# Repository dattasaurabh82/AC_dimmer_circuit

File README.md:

# AC_dimmer_circuit

Deisgend quickly in 2016 for [Politics of Power](http://www.dattasaurabh.com/Politics-of-Power)

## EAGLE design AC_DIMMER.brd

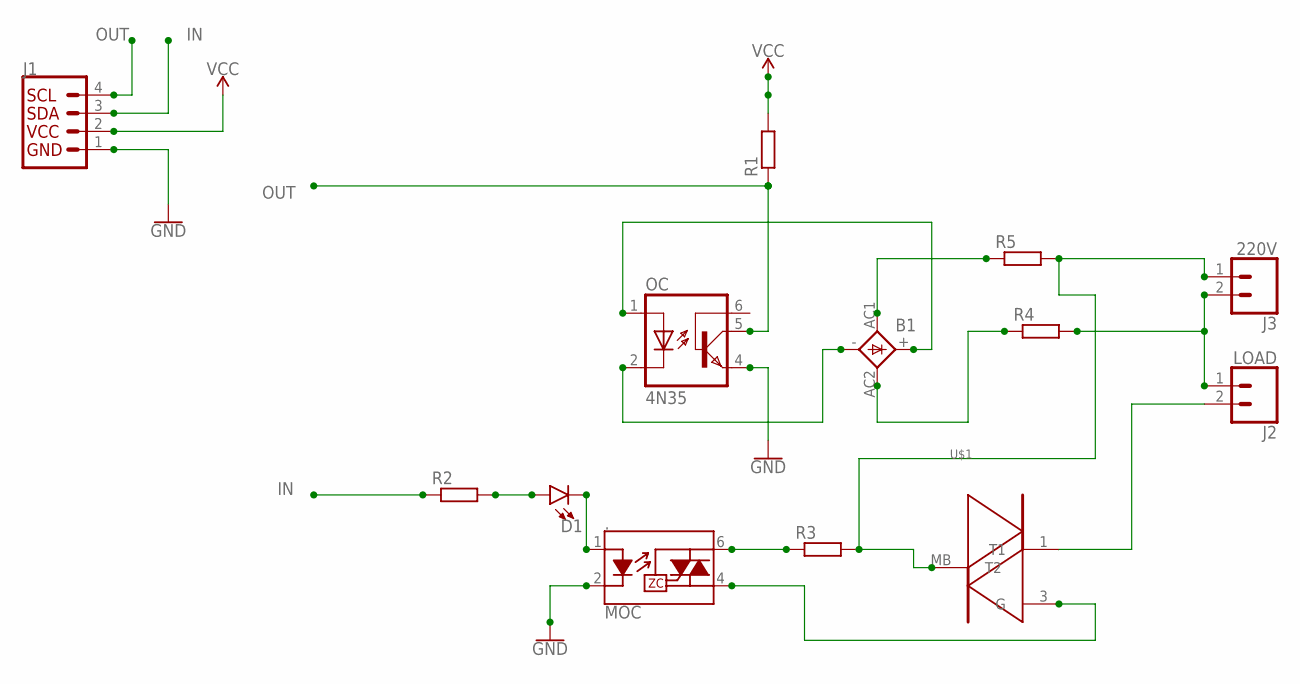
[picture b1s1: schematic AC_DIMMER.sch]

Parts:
.: MOC; DIP8SMD
B1: 2KBP
D1: LED-FKIT-1206; FKIT-LED-1206
J1: QWIIC_CONNECTORJS-1MM; 1X04_1MM_RA
J2: LOAD; SCREWTERMINAL-3.5MM-2
J3: 220V; SCREWTERMINAL-3.5MM-2
OC: 4N35; DIL6-SMD
R1, R2: RR0603; R0603
R3, R4, R5: R-EU_R3225; R3225
U$1: BT136S-600ETRIACA; SOT428

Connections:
GND: ..2 (K), J1.1 (GND), OC.4 (EMI)
IN: J1.3 (SDA), R2.1
unnamed: B1.+, OC.1 (A)
unnamed: B1.-, OC.2 (C)
unnamed: J2.2, U$1.1 (T1)
unnamed: D1.A, R2.2
unnamed: ..1 (A), D1.C
unnamed: J2.1, J3.2, R4.2
unnamed: ..6 (T1), R3.1
unnamed: B1.AC1, R5.1
unnamed: B1.AC2, R4.1
unnamed: ..4 (T2), U$1.3 (G)
unnamed: J3.1, R3.2, R5.2, U$1.MB (T2)
OUT: J1.4 (SCL), OC.5 (COL), R1.1
VCC: J1.2 (VCC), R1.2

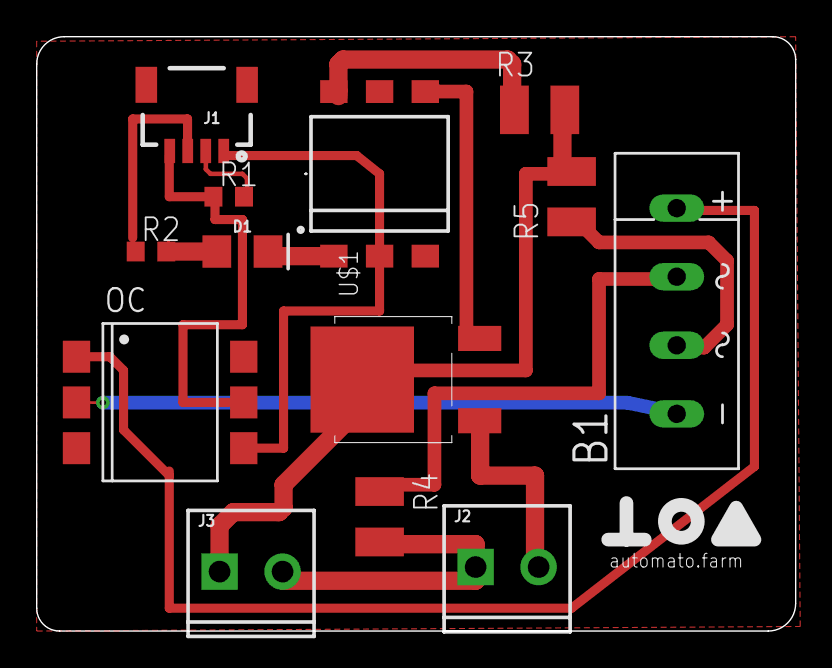
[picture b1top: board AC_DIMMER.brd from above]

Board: 2 copper layers, 42.2 x 33.0 mm, 13 parts (0 on the bottom side), 15 nets.

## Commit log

2017-12-13 ref image upload
2017-12-13 updaded image link in README

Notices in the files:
parts and their libraries:
SparkFun-DiscreteSemi: Licensing: Creative Commons ShareAlike 4.0 International - https://creativecommons.org/licenses/by-sa/4.0
